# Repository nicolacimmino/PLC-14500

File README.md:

**NEW!** You can now buy this as a ready to assemble kit on [tindie.com](https://www.tindie.com/products/28867/).

# Introduction

The PLC14500 Nano is a retro-style trainer board intended for the user to familiarize with the Motorola MC14500 1-bit
ICU (Industrial Control Unit), PLCs and Ladder Logic. The board has abundant LEDs that show the status of 
the system buses and registers. This, combined with the possibility to run the software step by step,
gives the user a great deal of insight into how their programs are executing. The slow clock mode 
makes instead for a mesmerizing light show that won't fail to impress when the board is parked on a desk,
waiting for the next coding adventure.

Main features:

* 256 Bytes of program RAM (can be replaced with an EEPROM)
* 7 Inputs each with toggle and momentary switch capability
* 7 Outputs (LEDs)
* 1 Timer mapped to the I/O bus (0.5 to 11s, adjustable via a trimmer)
* 7 bits scratchpad RAM
* 3 clock modes (fast, slow, manual step)

True to its retro style PLC14500 Nano sports exclusively through-hole components and chips in DIP packages.
You might notice an intruder in the Bill of Materials, an Arduino Nano! It's there purely to act as a
bootloader, with a convenient USB interface that surely is easy to connect to modern PCs. However,
to not spoil the illusion, the Arduino is mounted on the bottom side of the PCB, so it won't be visible when 
using the board.

This project is Open Source Hardware [Certified](https://certification.oshwa.org/pl000011.html)

# Toolchain

You can find all the tools to assemble and transfer programs ready built for Windows in the [releases](https://github.com/nicolacimmino/PLC-14500/releases) section.

In addition to the tools in this repo, Hein Pragt was so kind to build a workbench that you can use to simulate your programs while waiting to build the board. See an in-depth explanation of the MC14500 and of the tool on his [website](https://www.heinpragt.nl/?p=2749).

# Assembling the board

To keep the assembled board visually free from clutter, and to give more prominence to the labels
relevant in regular use, it was chosen to hide the component reference numbers on the silkscreen.
Where possible these are on the silkscreen under the component itself but, where not possible, 
these have been omitted completely. To help with the assembly please refer to the assembly view 
available in the `board` folder.

**NOTE** Make sure you refer to the right revision of the board matching the one you have. The board
revision can be found on the bottom side silk screen (eg `PLC14500 Nano REV.A`)

As usual start from the lower profile components (such as resistors and ICs), and work towards taller
profile ones, to finish with large caps and the trimmer. 

**NOTE** The Arduino Nano is to be assembled on the bottom side of the board, opposite the components,
as indicated in the silk screen. Also, make sure D40, D51, R54, C7 are soldered BEFORE you solder the 
Arduino as their PINs are under the Arduino board.

# Getting started

Download the latest toolchain (Windows only at the moment) from this Git repo [releases folder](https://github.com/nicolacimmino/PLC-14500/releases) and unzip it.

Before starting writing your programs and testing them on the board, you will need to flash the bootloader
into the Arduino. This can be easily done with the Arduino IDE. Load the sketch `bootloader.ino` from  the
release zip and make sure the board selected in the Arduino IDE is "Arduino Nano". Connect the board to your PC 
with a USB cable and select, in the Arduino IDE, the new serial port that will be assigned to the board. 
Upload the sketch and you are ready to go. Take note of the serial port name as you will need it to flash the
programs later.

Unless there will be an update to the bootloader you won't need to repeat this step in the future.

# Assembling a program

You can write your programs in a text editor of your choice, as long as you save them with a `.asm`
extension. This is a first example program to make sure your board is correctly assembled and functioning.
You can find this code also in the release zip file under `examples\smoketest.asm`.

````
.board=PLC14500-Nano

; *************************************************
; Prepare:
; All inputs off except IN6 (master switch).
; *************************************************

IEN IN6   ; IN6 acts as master switch
OEN IN6   ; to enable/disable all I/O

; *************************************************
; Test: Input and outputs are working correctly

LD  IN0   ; Load IN0,
AND IN1   ; logical AND it with IN1
STO OUT0  ; and show the result in OUT0.

; Expect: OUT0 is on only when both IN0 and IN1 are on.
; *************************************************

; *************************************************
; Test: TMR0 is working correctly

LD  IN2   ; Load IN2
STO OUT7  ; use it to trigger TMR0.

; Expect: Clicking IN2 on turns on IN7 (TMR0 output)
;   and, after few seconds, IN7 returns off.
; *************************************************

; *************************************************
; Test: Scratchpad RAM is working correctly.

LD  IN3    ; Copy IN3 to SPR0
STO SPR0

LD  SPR0   ; Copy SPR0 to SPR1
STO SPR1

; Expect: Clicking IN3 turns on SPR0 and SPR1
; *************************************************

JMP 0     ; Repeat.
````

Save it to a `test.asm` file and assemble it into a binary with the assembler found in the release zip file:

````
.\asm14500.exe .\test.asm
````

This will produce a `test.bin` file, which should be 256 bytes in size.

# Transferring a program to the board

To transfer the assembled `.bin` file to the board program RAM, make sure the USB cable is plugged in and take note of which serial port 
your board got mapped to in the Arduino IDE. You can then upload the flash command found in the release zip file:

````
.\flash14500 test.bin COM3
````

Replacing `COM3` with the correct port number for your board. Also remember to press the RST button on the board once the upload is done, and verify
that the top switches are in the "HI" and "RUN" positions respectively so the program runs.

# Testing

If you uploaded the above example program you can verify the board correct functioning by following the steps in the sourcecode that will guide you
through the needed settings and actions and expected outcomes.

**Help!!** some LEDs like `J`, `RR` or `W` randomly change intensity when I click other buttons. Do I have have a short somewhere? Did I break something? **no**,
don't worry. This is absolutely normal when the board is running on the normal clock (`HI` and `RUN`), this is because those LEDs are actually flashing on and off
as the MC14500 executes instructions. Because of the high clock speed you don't see the actual flickering but the resulting intensity depends on how often your program
causes them to be on (and for this reason, depending on the program, this is dependent on status of the inputs). This is also true for the `ADDR`, `DATA` and `SPR` LEDs when running with full clock. To convience yourself about this, and for a cool blinking effect, turn the clock to `LO` and watch, just don't expect outputs to react to your clicks promptly!

# What's next

Read more about the assembler and the `.asm` file syntax in the assembler folder [README.md](assembler/README.md).

To get started with programming your board and for some ideas of new programs you can try to make yourself, read the [Programmers Guide](assembler/programmers_guide.md).

If you find any issues, or want to contribute code/comments please feel free to use the "Issues" tool here on GitHub.

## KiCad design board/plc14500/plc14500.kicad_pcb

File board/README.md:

## REV_A -> REV_B

- Moved LED labelled HI to the left of LO (to match switch direction)

- Added 47K in series to U2 Pin3 OUT (to remove gosthing of outputs on inputs LEDs due to MC14500 W line timing)

- Passed OUT7 through a NOT before triggering TMR0, left LED direct to OUT7 (NE555 triggers on low which makes it hakward without negation as the monostable triggers always once on reset)

- Swapped RV1 Pin3 and Pin1 (so clockwise rotation increases time)

*NOTE* REV.A was never on sale, it was a pre-production proto. If you have got a REV.A you either got a
knockoff by someone who got the gerbers in the early days or somehow you got hold of a display unit
from a museum.

## REV_B -> REV_C

- Replaced SPR7 with RR so that RR can be read at IO $7
- Replaced C4 with a 10uF and RV1 with 1M. Similar timing but more consistent when triggered by short pulses.

  (Thanks to [wrh3c](https://github.com/wrh3c) for the suggestion).

If you have a REV.B and you are interested in experimenting with the ION/OEN driven if/else structures
described in the Motorola's own MC14500 Handbook, you will need a tiny modification to the board. This
will replace SPR7 input signal with RR so that you can control IEN/OEN registers fully.

- Cut pin 1 of U13 (isolates the Q7 output of the CD4099, leaving what used to be SPR7 floating )
- Connect the **pad** of pin 1 of U13 to pin 15 of U10 (thus connecting the MC14500 RR to what used to be SPR7 input)
- If having the SPR7 LED confuses you, cut LED D50

## REV_C -> REV_D

- Corrected clock source to feed into X2 and used X1 to drive the counter. There are no functional changes.

- Added LEDs also for RTN, FLAG0, FLAGF. Even though these signals are not relevant for this design
	many asked to have them visible for educational purpuses.

- Rearranged ADDR, DATA, SPR LEDs to have lsb on the right.

- Rearranged OUT LEDs in a more compact layout like the others.

- Added an expansion connector to use external inputs/outputs.

- Swapped around the wiring of input switches so that right is ON left is OFF.

- Swapped around the wiring of the clock switches so that HI and RUN are on the right.

## REV_D Artifacts

Silk

Assembly

Top

Bottom

## REV_C Artifacts

Silk

Assembly

Top

Bottom

## REV_B Artifacts

Silk

Assembly

Top

Bottom

## REV_A Artifacts

Silk

Assembly

Top

Bottom

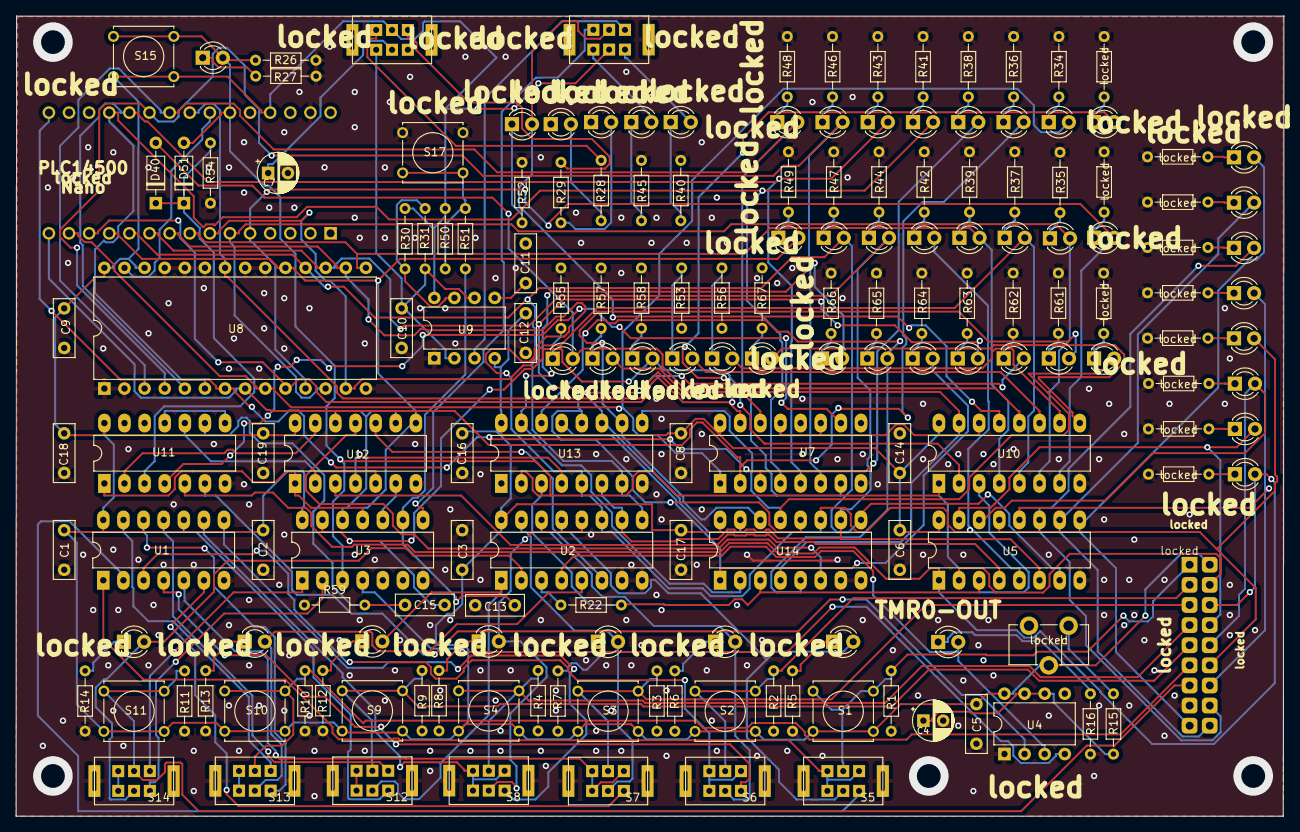
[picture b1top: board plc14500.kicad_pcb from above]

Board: 2 copper layers, 160.1 x 101.0 mm, 173 parts (1 on the bottom side), 157 nets.

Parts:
C1, C2, C3, C5, C6, C8, C9, C10, C11, C12, C13, C14, C15, C16, C17, C18, C19: 100nF; C_Rect_L7.2mm_W2.5mm_P5.00mm_FKS2_FKP2_MKS2_MKP2
C4: 10uF; CP_Radial_D5.0mm_P2.50mm
C7: 470uF; CP_Radial_D5.0mm_P2.50mm
D1, D2, D3, D4, D5, D6, D7, D8, D9, D10, D11, D12, D13, D14, D15, D16, D17, D20, D21, D22, D23, D24, D25, D26, D27, D29, D30, D31, D32, D34, D35, D36, D37, D43, D44, D45, D46, D47, D48, D49: LED 3MM Red; LED_3MM
D18, D19, D28, D33, D38: LED 3MM Yellow; LED_3MM
D39, D41, D42, D50, D52, D53: LED 3MM Orange; LED_3MM
D40, D51: 1N4148; D_DO-35_SOD27_P7.62mm_Horizontal
R1, R2, R3, R4, R9, R10, R11, R22, R26: 47K; R_Axial_DIN0204_L3.6mm_D1.6mm_P7.62mm_Horizontal
R5, R6, R7, R8, R12, R13, R14, R16, R27, R28, R29, R34, R35, R36, R37, R38, R39, R40, R41, R42, R43, R44, R45, R46, R47, R48, R49, R52, R53, R55, R56, R57, R58, R59, R61, R62, R63, R64, R65, R66, R67: 820R; R_Axial_DIN0204_L3.6mm_D1.6mm_P7.62mm_Horizontal
R15: 2K2; R_Axial_DIN0204_L3.6mm_D1.6mm_P7.62mm_Horizontal
R30, R31: 1K; R_Axial_DIN0204_L3.6mm_D1.6mm_P7.62mm_Horizontal
R50, R51, R54: 10K; R_Axial_DIN0204_L3.6mm_D1.6mm_P7.62mm_Horizontal
S1, S2, S3, S4, S9, S10, S11, S15, S17: Push Button; SW_Tactile_THT
S5, S6, S7, S8, S12, S13, S14, S16, S18: Switch DPDT; SWITCH_DPDT
U1, U3, U11: 74HC14; DIP-14_W7.62mm_LongPads
U2, U14: 4051; DIP-16_W7.62mm_LongPads
U4, U9: NE555; DIP-8_W7.62mm
U5, U13: 4099; DIP-16_W7.62mm_LongPads
U6: Arduino Nano; Arduino_Nano
U7: 74HC590A; DIP-16_W7.62mm_LongPads
U8: LH5168; DIP-28_W15.24mm
U10: MC14500; DIP-16_W7.62mm_LongPads
U12: 4011; DIP-14_W7.62mm_LongPads
locked: 820R; R_Axial_DIN0204_L3.6mm_D1.6mm_P7.62mm_Horizontal
locked#2, locked#3, locked#4, locked#5, locked#6, locked#7, locked#8, locked#9, locked#10, locked#11: 820R; R_Axial_DIN0204_L3.6mm_D1.6mm_P7.62mm_Horizontal
locked#12: 1M; HORIZONTAL_POT
locked#13: PLC14500-Expansion

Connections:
+5V: C1.2, C2.2, C3.1, C5.1, C6.1, C8.1, C9.2, C12.2, C14.1, C16.1, C17.1, C18.2, C19.2, R30.2, R50.2, S1.2, S2.2, S3.2, S4.2, S9.2, S10.2, S11.2, S15.2, S16.2, S18.6, U1.14 (VCC), U2.16 (VDD), U3.14 (VCC), U4.8 (VCC+), U5.16 (VCC), U6.27 (+5V), U7.16 (VCC), U8.26 (A13), U8.28 (VCC), U9.4 (/RES), U9.8 (VCC+), U10.16 (Vcc), U11.14 (VCC), U12.14 (VDD), U13.16 (VCC), U14.16 (VDD), locked#12.2, locked#13.18 (+5v)
/!RES: U3.4, U4.4 (/RES)
/!WEN: U6.24 (A5), U8.27 (~WE)
/A0: D20.A, U6.13 (D10), U7.15 (Q0), U8.10 (A0)
/A1: D22.A, U6.14 (D11), U7.1 (Q1), U8.9 (A1)
/A2: D24.A, U6.15 (D12), U7.2 (Q2), U8.8 (A2)
/A3: D26.A, U6.16 (D13), U7.3 (Q3), U8.7 (A3)
/A4: D29.A, U6.19 (A0), U7.4 (Q4), U8.6 (A4)
/A5: D31.A, U6.20 (A1), U7.5 (Q5), U8.5 (A5)
/A6: D34.A, U6.21 (A2), U7.6 (Q6), U8.4 (A6)
/A7: D36.A, U6.22 (A3), U7.7 (Q7), U8.3 (A7)
/CPU/CLK1: U7.11 (CPC), U7.13 (CPR), U10.14 (X1)
/CPU/CLK2: D38.A, S18.2, U10.13 (X2)
/CPU/JMP: D39.A, D40.2 (A), U10.12 (JMP)
/D: R22.2, U5.3 (D), U10.3 (D), U13.3 (D), U14.3 (X)
/D0: D21.A, U6.5 (D2), U8.11 (Q0), U10.7 (I0)
/D1: D23.A, U6.6 (D3), U8.12 (Q1), U10.6 (I1)
/D2: D25.A, U6.7 (D4), U8.13 (Q2), U10.5 (I2)
/D3: D27.A, U6.8 (D5), U8.15 (Q3), U10.4 (I3)
/D4: D30.A, U2.11 (A), U5.5 (A0), U6.9 (D6), U8.16 (Q4), U13.5 (A0), U14.11 (A)
/D5: D32.A, U2.10 (B), U5.6 (A1), U6.10 (D7), U8.17 (Q5), U13.6 (A1), U14.10 (B)
/D6: D35.A, U2.9 (C), U5.7 (A2), U6.11 (D8), U8.18 (Q6), U13.7 (A2), U14.9 (C)
/D7: D37.A, U3.11, U6.12 (D9), U8.19 (Q7), U11.1, U12.1, U12.8
/IN-INH: U2.6 (Inh), U12.10
/Input-Output/EXTIN0: R1.2, S1.1, S5.6, locked#13.1 (EXTIN0)
/Input-Output/EXTIN1: R2.2, S2.1, S6.6, locked#13.2 (EXTIN1)
/Input-Output/EXTIN2: R3.2, S3.1, S7.6, locked#13.3 (EXTIN2)
/Input-Output/EXTIN3: R4.2, S4.1, S8.6, locked#13.4 (EXTIN3)
/Input-Output/EXTIN4: R9.2, S9.1, S12.6, locked#13.5 (EXTIN4)
/Input-Output/EXTIN5: R10.2, S10.1, S13.6, locked#13.6 (EXTIN5)
/Input-Output/EXTIN6: R11.2, S11.1, S14.6, locked#13.7 (EXTIN6)
/Input-Output/IN0: D1.A, S5.2, U2.13 (X0)
/Input-Output/IN1: D2.A, S6.2, U2.14 (X1)
/Input-Output/IN2: D3.A, S7.2, U2.15 (X2)
/Input-Output/IN3: D4.A, S8.2, U2.12 (X3)
/Input-Output/IN4: D5.A, S12.2, U2.1 (X4)
/Input-Output/IN5: D6.A, S13.2, U2.5 (X5)
/Input-Output/IN6: D7.A, S14.2, U2.2 (X6)
/Input-Output/IN7: D8.A, U2.4 (X7), U4.3 (OUT)
/Input-Output/OUT0: D16.A, U5.9 (Q0), locked#13.9 (OUT0)
/Input-Output/OUT1: D15.A, U5.10 (Q1), locked#13.10 (OUT1)
/Input-Output/OUT2: D14.A, U5.11 (Q2), locked#13.11 (OUT2)
/Input-Output/OUT3: D13.A, U5.12 (Q3), locked#13.12 (OUT3)
/Input-Output/OUT4: D12.A, U5.13 (Q4), locked#13.13 (OUT4)
/Input-Output/OUT5: D11.A, U5.14 (Q5), locked#13.14 (OUT5)
/Input-Output/OUT6: D10.A, U5.15 (Q6), locked#13.15 (OUT6)
/OUT-WD: U5.4 (WD), U12.3
/PRG: U6.23 (A4), U7.14 (~OE), U8.22 (~OE)
/RES: D17.A, D51.2 (A), R26.1, S15.1, U3.3, U5.2 (RST), U6.25 (A6), U10.1 (RST), U13.2 (RST), locked#13.17 (RST)
/RR: D41.A, U10.15 (RR), U14.4 (X7)
/SPRAM/SPRAM-INH: U12.11, U14.6 (Inh)
/SPRAM/SPRAM-WD: U12.4, U13.4 (WD)
/TMR0-TRG: D9.A, U5.1 (Q7), U11.5, locked#13.16 (OUT7)
/W: C15.2, D42.A, U3.13, U10.2 (WRITE)
GND: C1.1, C2.1, C3.2, C4.2, C5.2, C6.2, C7.2, C8.2, C9.1, C10.2, C11.2, C12.1, C13.1, C14.2, C16.2, C17.2, C18.1, C19.1, D18.K (C), D19.K (C), R1.1, R2.1, R3.1, R4.1, R5.1, R6.1, R7.1, R8.1, R9.1, R10.1, R11.1, R12.1, R13.1, R14.1, R16.2, R26.2, R27.2, R34.1, R35.1, R36.1, R37.1, R38.1, R39.1, R40.1, R41.1, R42.1, R43.1, R44.1, R45.1, R46.1, R47.1, R48.1, R49.1, R52.1, R53.1, R54.1, R55.1, R56.1, R57.1, R58.1, R59.1, R61.1, R62.1, R63.1, R64.1, R65.1, R66.1, R67.1, S5.8 (GND), S5.9 (GND), S6.8 (GND), S6.9 (GND), S7.8 (GND), S7.9 (GND), S8.8 (GND), S8.9 (GND), S12.8 (GND), S12.9 (GND), S13.8 (GND), S13.9 (GND), S14.8 (GND), S14.9 (GND), S16.8 (GND), S16.9 (GND), S17.1, S18.8 (GND), S18.9 (GND), U1.7 (GND), U2.7 (VEE), U2.8 (VSS), U3.7 (GND), U4.1 (GND), U5.8 (GND), U6.4 (GND), U6.29 (GND), U7.8 (GND), U7.12 (~CE), U8.1 (A14), U8.2 (A12), U8.14 (GND), U8.20 (~CS), U8.21 (A10), U8.23 (A11), U8.24 (A9), U8.25 (A8), U9.1 (GND), U10.8 (GND), U11.7 (GND), U12.7 (VSS), U13.8 (GND), U14.7 (VEE), U14.8 (VSS), locked.1, locked#2.1, locked#3.1, locked#4.1, locked#5.1, locked#6.1, locked#7.1, locked#8.1, locked#9.1, locked#10.1, locked#11.1, locked#13.8 (GND)
unnamed: C7.1, S16.6
unnamed: C13.2, R51.1, U3.9
unnamed: C15.1, R59.2, U11.9
unnamed: D1.K (C), R5.2
unnamed: D2.K (C), R6.2
unnamed: D3.K (C), R7.2
unnamed: D4.K (C), R8.2
unnamed: D5.K (C), R12.2
unnamed: D6.K (C), R13.2
unnamed: D7.K (C), R14.2
unnamed: D8.K (C), R16.1
unnamed: D9.K (C), locked.2
unnamed: D10.K (C), locked#2.2
unnamed: D11.K (C), locked#3.2
unnamed: D12.K (C), locked#4.2
unnamed: D13.K (C), locked#5.2
unnamed: D14.K (C), locked#6.2
unnamed: D15.K (C), locked#7.2
unnamed: D16.K (C), locked#8.2
unnamed: D17.K (C), R27.1
unnamed: D18.A, R29.2
unnamed: D19.A, R28.2
unnamed: D20.K (C), locked#9.2
unnamed: D21.K (C), locked#10.2
unnamed: D22.K (C), R34.2
unnamed: D23.K (C), R35.2
unnamed: D24.K (C), R36.2
unnamed: D25.K (C), R37.2
unnamed: D26.K (C), R38.2
unnamed: D27.K (C), R39.2
unnamed: D28.K (C), R40.2
unnamed: D28.A, S18.5
unnamed: D29.K (C), R41.2
unnamed: D30.K (C), R42.2
unnamed: D31.K (C), R43.2
unnamed: D32.K (C), R44.2
unnamed: D33.K (C), R45.2
unnamed: D33.A, S18.7
unnamed: D34.K (C), R46.2
unnamed: D35.K (C), R47.2
unnamed: D36.K (C), R48.2
unnamed: D37.K (C), R49.2
unnamed: D38.K (C), R52.2
unnamed: D39.K (C), R55.2
unnamed: D40.1 (K), D51.1 (K), R54.2, U11.3
unnamed: D41.K (C), R57.2
unnamed: D42.K (C), R58.2
unnamed: D43.K (C), locked#11.2
unnamed: D44.K (C), R61.2
unnamed: D45.K (C), R62.2
unnamed: D46.K (C), R63.2
unnamed: D47.K (C), R64.2
unnamed: D48.K (C), R65.2
unnamed: D49.K (C), R66.2
unnamed: D50.K (C), R53.2
unnamed: D52.K (C), R56.2
unnamed: D53.K (C), R67.2
unnamed: R15.1, locked#12.1
unnamed: R28.1, S16.3
unnamed: R29.1, S16.1
unnamed: R50.1, R51.2, S17.2
unnamed: S5.1, S5.5, S5.7, U1.1
unnamed: S5.3, U1.2
unnamed: S6.1, S6.5, S6.7, U1.3
unnamed: S6.3, U1.4
unnamed: S7.1, S7.5, S7.7, U1.5
unnamed: S7.3, U1.6
unnamed: S8.1, S8.5, S8.7, U1.9
unnamed: S8.3, U1.8
unnamed: S12.1, S12.5
unnamed: S12.3, U1.10
unnamed: S12.7, U1.11
unnamed: S13.1, S13.5
unnamed: S13.3, U1.12
unnamed: S13.7, U1.13
unnamed: S14.1, S14.5
unnamed: S14.3, U3.2
unnamed: S14.7, U3.1
unnamed: S18.3, U3.8
unnamed: R22.1, U2.3 (X)
unnamed: C4.1, R15.2, U4.6 (TRE), U4.7 (DIS)
unnamed: U4.2 (TRI), U11.6
unnamed: U7.10 (~MRC), U11.4
unnamed: C11.1, U9.5 (CON)
unnamed: R30.1, R31.2, U9.7 (DIS)
unnamed: S18.1, U9.3 (OUT)
unnamed: C10.1, R31.1, S16.7, U9.2 (TRI), U9.6 (TRE)
unnamed: D52.A, U10.10 (FLAG0)
unnamed: D53.A, U10.9 (FLAGF)
unnamed: D50.A, U10.11 (RTN)
unnamed: U11.2, U12.13
unnamed: U11.10, U12.2, U12.5
unnamed: U11.8, U11.11
unnamed: U3.10, U12.6
unnamed: U3.12, U12.9, U12.12
unnamed: D43.A, U13.9 (Q0), U14.13 (X0)
unnamed: D44.A, U13.10 (Q1), U14.14 (X1)
unnamed: D45.A, U13.11 (Q2), U14.15 (X2)
unnamed: D46.A, U13.12 (Q3), U14.12 (X3)
unnamed: D47.A, U13.13 (Q4), U14.1 (X4)
unnamed: D48.A, U13.14 (Q5), U14.5 (X5)
unnamed: D49.A, U13.15 (Q6), U14.2 (X6)

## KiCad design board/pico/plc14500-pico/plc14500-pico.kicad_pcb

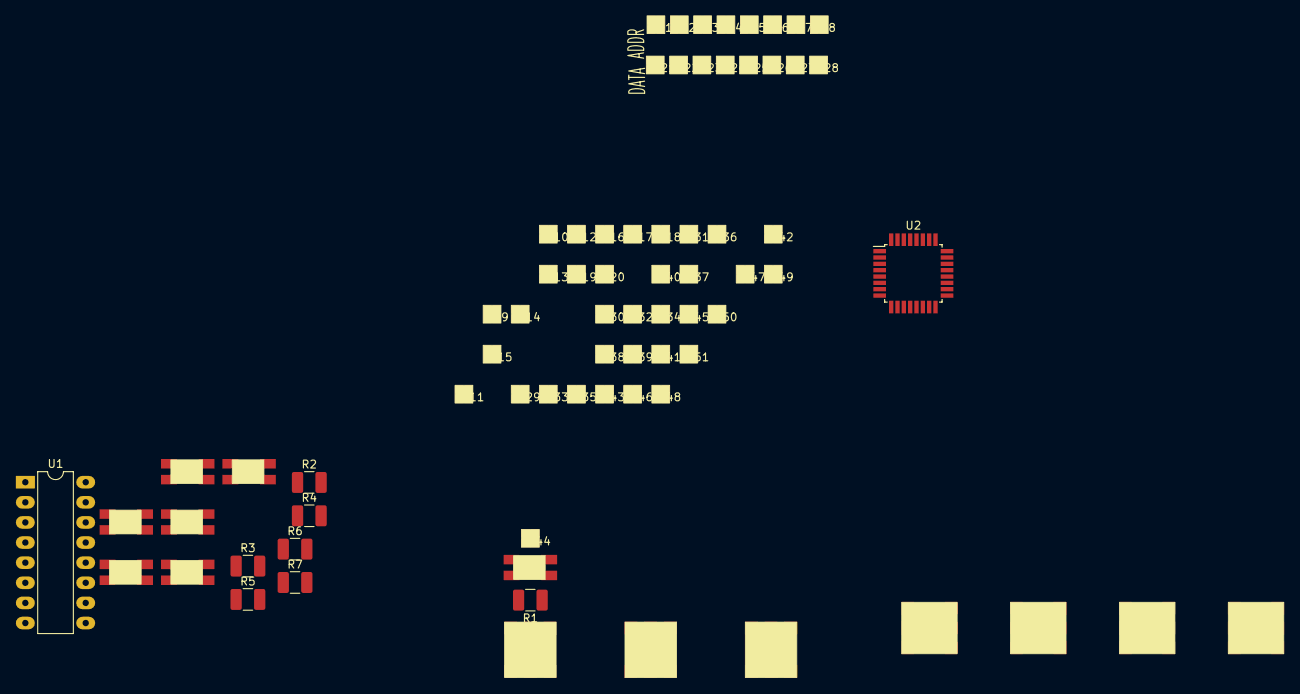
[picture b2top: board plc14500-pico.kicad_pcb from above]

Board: 2 copper layers, 74 parts (0 on the bottom side), 73 nets, no tracks yet.

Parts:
D1, D2, D3, D4, D5, D6, D7, D8, D9, D10, D11, D12, D13, D14, D15, D16, D17, D18, D19, D20, D21, D22, D23, D24, D25, D26, D27, D28, D29, D30, D31, D32, D33, D34, D35, D36, D37, D38, D39, D40, D41, D42, D43, D44, D45, D46, D47, D48, D49, D50, D51: WS2812B; WS2812-2020
R1, R2, R3, R4, R5, R6, R7: R; R_1210_3225Metric_Pad1.42x2.65mm_HandSolder
SW1, SW3, SW5, SW7, SW9, SW11, SW13: SW_Push_DPDT; DPDT_SMD
SW2, SW4, SW6, SW8, SW10, SW12, SW14: SW_MEC_5G; TACTILE_SWITCH_SMD_3_3
U1: MC14500; DIP-16_W7.62mm_LongPads
U2: ATmega328P-AU-Edited; TQFP-32_7x7mm_P0.8mm

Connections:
+5V: D1.4, D2.4, D3.4, D4.4, D5.4, D6.4, D7.4, D8.4, D9.4, D10.4, D11.4, D12.4, D13.4, D14.4, D15.4, D16.4, D17.4, D18.4, D19.4, D20.4, D21.4, D22.4, D23.4, D24.4, D25.4, D26.4, D27.4, D28.4, D29.4, D30.4, D31.4, D32.4, D33.4, D34.4, D35.4, D36.4, D37.4, D38.4, D39.4, D40.4, D41.4, D42.4, D43.4, D44.4, D45.4, D46.4, D47.4, D48.4, D49.4, D50.4, D51.4, SW1.1, SW1.6, SW3.1, SW3.6, SW5.1, SW5.6, SW7.1, SW7.6, SW9.1, SW9.6, SW11.1, SW11.6, SW13.6
GND: D1.2, D2.2, D3.2, D4.2, D5.2, D6.2, D7.2, D8.2, D9.2, D10.2, D11.2, D12.2, D13.2, D21.2, D22.2, D23.2, D24.2, D25.2, D26.2, D27.2, D28.2, D29.2, D30.2, D31.2, D32.2, D33.2, D34.2, D35.2, D36.2, D37.2, D38.2, D39.2, D40.2, D41.2, D42.2, D43.2, D44.2, D45.2, D46.2, D47.2, D48.2, D49.2, D50.2, D51.2, SW1.3, SW1.4, SW3.3, SW3.4, SW5.3, SW5.4, SW7.3, SW7.4, SW9.3, SW9.4, SW11.3, SW11.4, SW13.3, SW13.4
unnamed: D1.1, D2.3
unnamed: D2.1, D3.3
unnamed: D3.1, D4.3
unnamed: D4.1, D5.3
unnamed: D5.1, D6.3
unnamed: D6.1, D7.3
unnamed: D7.1, D8.3
unnamed: D8.1, D9.3
unnamed: D10.1, D11.3
unnamed: D9.1, D10.3
unnamed: D11.1, D12.3
unnamed: D12.1, D13.3
unnamed: D13.1, D21.3
unnamed: D14.1, D15.3
unnamed: D14.2, D15.2, D16.2, D17.2, D18.2, D19.2, D20.2
unnamed: D15.1, D16.3
unnamed: D16.1, D17.3
unnamed: D17.1, D18.3
unnamed: D18.1, D19.3
unnamed: D19.1, D20.3
unnamed: D21.1, D22.3
unnamed: D22.1, D23.3
unnamed: D23.1, D24.3
unnamed: D24.1, D25.3
unnamed: D25.1, D26.3
unnamed: D26.1, D27.3
unnamed: D27.1, D28.3
unnamed: D29.1, D30.3
unnamed: D30.1, D31.3
unnamed: D31.1, D32.3
unnamed: D32.1, D33.3
unnamed: D33.1, D34.3
unnamed: D34.1, D35.3
unnamed: D35.1, D36.3
unnamed: D36.1, D37.3
unnamed: D37.1, D38.3
unnamed: D38.1, D39.3
unnamed: D39.1, D40.3
unnamed: D40.1, D41.3
unnamed: D41.1, D42.3
unnamed: D42.1, D43.3
unnamed: D44.1, D45.3
unnamed: D45.1, D46.3
unnamed: D46.1, D47.3
unnamed: D47.1, D48.3
unnamed: D48.1, D49.3
unnamed: D49.1, D50.3
unnamed: D50.1, D51.3
unnamed: R1.1, SW2.3, SW2.4
unnamed: R1.2, SW1.5
unnamed: R2.1, SW4.3, SW4.4
unnamed: R2.2, SW3.5
unnamed: R3.1, SW6.3, SW6.4
unnamed: R3.2, SW5.5
unnamed: R4.1, SW8.3, SW8.4
unnamed: R4.2, SW7.5
unnamed: R5.1, SW10.3, SW10.4
unnamed: R5.2, SW9.5
unnamed: R6.1, SW12.3, SW12.4
unnamed: R6.2, SW11.5
unnamed: R7.1, SW14.3, SW14.4
unnamed: R7.2, SW13.5
unnamed: SW1.2, SW2.1, SW2.2
unnamed: SW3.2, SW4.1, SW4.2
unnamed: SW5.2, SW6.1, SW6.2
unnamed: SW7.2, SW8.1, SW8.2
unnamed: SW9.2, SW10.1, SW10.2
unnamed: SW11.2, SW12.1, SW12.2
unnamed: SW13.2, SW14.1, SW14.2
unnamed: U2.4, U2.6
unnamed: U2.3, U2.5, U2.21

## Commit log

2015-02-01 Implemented uploading of code from serial
2015-02-01 Added Compiler application
2015-02-01 Added board picture
2015-02-03 Updated board picture
2015-02-03 Updated board image
2015-02-03 Added full resolution board image
2015-02-03 Fixed issues with programmer not releasing bus
2015-02-03 Code cleanup
2015-02-03 Added scope capture for write line problem
2015-02-03 Added monostable schematic
2015-02-03 Updated capture
2015-02-04 Added schematic
2015-02-04 Corrected schematic
2022-11-03 Add board
2022-11-05 Schema
2022-11-07 Schema updates, add loopback and timer
2022-11-09 Add assembler skeleton
2022-11-09 Add scratchpad ram
2022-11-09 Schematic tweaks
2022-11-09 ignore .exe
2022-11-09 First working assembler proto
2022-11-12 All components on the board! WIP
2022-11-12 Board preview
2022-11-12 Remove old assembler
2022-11-12 Remove old schema
2022-11-13 Better tests
2022-11-13 Fix JMP
2022-11-13 Add simulator scaffolding
2022-11-13 Pass status to output
2022-11-14 Lift state
2022-11-14 Bit of cleanup
2022-11-14 Cleanup, fix tests
2022-11-14 Cleanup, refactor
2022-11-14 Add some tests for mc14500.dart
2022-11-14 Add ADRs
2022-11-14 Rename
2022-11-16 Board routing
2022-11-16 Nano board rev-a prod ready
2022-11-16 Few more blocks
2022-11-17 Add load
2022-11-17 Honour IEN/OEN
2022-11-17 Fix IEN/OEN
2022-11-17 Add TMR0
2022-11-17 Add press button as on board
2022-11-17 Add some graphics
2022-11-18 Update board 3d models
2022-11-20 Refactor
2022-11-21 Pad binary to 256 bytes
2022-11-21 Add metadata to assembler
2022-11-22 tmp rename
2022-11-22 Trim
2022-11-22 clean
2022-11-22 Web scaffolding
2022-11-22 Add board svgs
2022-11-22 Add load button to simulator
2022-11-23 Add instructions
2022-11-23 Cleanup
2022-11-23 Add schematic in PDF format for easier peruse
2022-11-25 Fix bootloader, add labels to aseembler
2022-11-27 First release artifacts
2022-11-28 Add build script, some kit packaging material
2022-11-28 Scripts tweaks
2022-11-28 Cleanup release script, add smoketest
2022-11-28 Add build release command
2022-11-28 Fix input control
2022-11-29 Add oshw cert, add missing drill file
2022-11-29 Add small cert
2022-11-29 Refactor, add board specific code
2022-11-30 Programmers guide, WIP
2022-11-30 missing image
2022-11-30 developers guide, WIP
2022-11-30 Readme updates
2022-11-30 Move
2022-11-30 Simulator screenshot
2022-11-30 Remove web folder
2022-12-06 Rev_b board
2022-12-29 Cleanup simulator, examples
2023-01-02 Updates in preparation for rel 1
2023-01-03 Small fixes to schema/assembly layout after test assembly
2023-01-03 Leaflet, fix couple of typos
2023-01-04 Fix Arduino label to fit ziplock
2023-01-17 Add Arduino installation note
2023-02-06 Update bom and assembly plan for new RAM code
2023-02-12 Tweak BOM
2023-02-17 Rescue some missing symbols that were broken
2023-02-17 Add kill the bit game example, tweaks to the assembled for REV.C
2023-02-17 Modify Killthebit so it can work even without the RR register mapped to SPR0
2023-02-17 Prepare for an eventual REV.C with RR mapped to SPR0 (remove usage of SPR0 from examples).
2023-02-17 Nicola/rev c preparations (#1)
    * Add kill the bit game example
    * Prepare for an eventual REV.C with RR mapped to SPR0 (remove usage of SPR0 from examples).
2023-02-17 Update killthebit.asm
    Typo
2023-02-19 Experimental: assemble using cc65
2023-02-19 Make mnemonics case-insensitive
2023-02-20 Add kill-the-bit to cc65 examples
2023-03-09 Add note on modifying REV.B for RR mapping to I/O
2023-03-11 Move assembler extension for CC65 to a separate repo
2023-03-11 rev.c board
2023-03-11 Add comments and IO map
2023-03-11 Fix rev.b->c instructions
2023-03-11 Kill the bit cleanup
2023-03-11 rev.b/c split
2023-03-11 Cleanup/fix programmers guide and examples
2023-03-16 Rev.C cleanup, a rough proto of an Assembler/Monitor
2023-03-17 Change C4/RV1, update "killthebit" example for better playability
2023-03-17 REV.C (#6)
    REV.C board updates
2023-03-17 Make JMP to non-zero a warning
2023-03-18 Mon14500
2023-03-19 Finalize commands, cleanup
2023-03-20 Add comments
2023-03-20 Mon14500, still WIP but usable (#7)
2023-03-21 Fix build release command
2023-03-26 Messages cleanup
2023-03-29 Add load/save, make assembled program runnable immediately
2023-03-31 Fix few annoying bugs
2023-03-31 14500MON Final touches
2023-04-01 Cleanup readme
2023-04-01 Add 14500MON screenshot
2023-04-01 Add credit
2023-04-01 Nicola/14500mon (#8)
    * Messages cleanup
    * Refactor
    * Refactor
    * Refactor
    * Add load/save, make assembled program runnable immediately
    * Fix few annoying bugs
2023-04-21 Add REV.C board renders
2023-04-21 Rescale pics
2023-05-10 Fix Assemble command doesn't take HEX arguments. Thanks, Bernard, for noticing.
2023-05-10 Pico first draft
2023-10-26 Convert to kicad7.0
2024-01-25 Fix smoketest.asm to match printed leaflets
2024-02-05 Fix typo
2024-02-12 Remove kicad backups
2024-02-12 Rearrange LEDs
2024-02-12 Ignore backup files from kicad
2024-02-17 REV.D Schema updates
2024-02-17 Restore PCB anchoring holes
2024-02-17 Address ERC errors
2024-02-17 Cleanup, ready to route
2024-02-19 REV.D first proto
2024-03-07 Fix issues on REV.D0
2024-03-09 REV.D schema fixes, better assembler output, some docs
2024-03-09 Add ignore of kicad lock files
2024-04-09 REV.C
2024-04-09 More examples for board rev. c (#16)
    * REV.C
    * REV.C
2024-04-28 Fix flash command to work with COM above 9
2024-05-26 remove backup
2024-05-26 Ingore board backups
2024-05-26 Add 14500MON labels
2024-05-26 Rearrange folders
2024-05-27 Add 14500MON bootloader config shortcut
2024-05-27 Tweaks to bootconfig
2024-08-06 Fix assembler.dart is gitignored
2024-08-07 Update README.md
    Fix reference to CC64 assembler repo
2024-08-19 First tests for a rust upload tool, WIP
2024-08-19 Fixes
2024-08-19 route
2024-08-19 Re-route REV.D, fab files next round
2024-08-19 Rev.d
2024-08-19 Added reset cap from program line
2024-08-20 REV.D artifacts
2024-08-20 Cleanup REV.D
2024-08-20 Remove old file
2024-08-20 Feature/rev.d (#19)
    * First tests for a rust upload tool, WIP
    * Rearrange LEDs
    * Remove kicad backups
    * REV.D Schema updates
    * Restore PCB anchoring holes
    * Address ERC errors
2024-08-20 Remove left over folder, was moved to tools
2024-08-20 Generate new 3d view
2024-09-04 Clear OUT and SPR on program
2024-09-04 Fix RST line pulsing on program upload doesn't work
2024-09-04 Bump bootloader version to 1.3
2024-09-04 Fix/rst line (#20)
    * Clear OUT and SPR on program
    * Fix RST line pulsing on program upload doesn't work
    * Bump bootloader version to 1.3
2024-11-12 * added build_release.sh for macOS (and linux?) * added link to Dart Install * ignored user compiled programs in tools/assember/examples/*.bin
2024-11-13 * added build_release.sh for macOS (and linux?) (#21)
    * added link to Dart Install
    * ignored user compiled programs in tools/assember/examples/*.bin
2025-03-25 rearranged flash-rs to handle keyboard input and serial communication asynchronously
2025-06-30 Fleshed out flash-rs, so it can successfully upload a program and then fall into the interactive monitor. It can become stuck in the trace routine, but you can get it out by switching to the fast mod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
2025-06-30 Added README.md to flash-rs
2025-07-13 flash-rs fleshed out (#22)
    * rearranged flash-rs to handle keyboard input and serial communication asynchronously
    * Fleshed out flash-rs, so it can successfully upload a program and then fall into the interactive monitor. It can become stuck in the trace routine, but you can get it out by switching to the fast m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
    * Added README.md to flash-rs
    ---------
2026-04-27 New experimental unified tool
2026-04-27 New experimental unified tool (#23)
    Assembler and uploader.
    Works in Linux and Windows with gitBash at least.
